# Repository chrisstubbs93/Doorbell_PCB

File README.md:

# Lecturer Availability Door Announcer

## Abstract
Traditionally a student would have to summon a lecturer in a shared office by knocking on the door. This disturbs the other lecturers in the office, and the desired lecturer may not even be present.

A system to alert a specific lecturer to the presence of someone at the door is not currently widely adopted. To investigate how such a system should work, it is crucial to gain insight into the current solutions to the individual technical challenges.

## Introduction
The main aim of this project is to develop a battery-operated device with inputs to receive interaction from the student, and outputs to feed back to the student and lecturer. It is to be fixed to the inside of the door of a multiple occupied lecturer's room. Through this device anyone outside the door shall be able to raise the attention of a single lecturer, and not to everyone in the room (which is what knocking at the door does). When a student operates the device, a notification should be sent to the appropriate lecturer’s mobile phone. It should also be possible for students to see the status/availability of a lecturer from the device, which the lecturer can set.

## Hardware

 - ESP32-WROOM-32
 - Waveshare 2.9" B/W ePaper
 - TCA9548A i2c multiplexer
 - VCNL4020 IR proximity sensor(s)

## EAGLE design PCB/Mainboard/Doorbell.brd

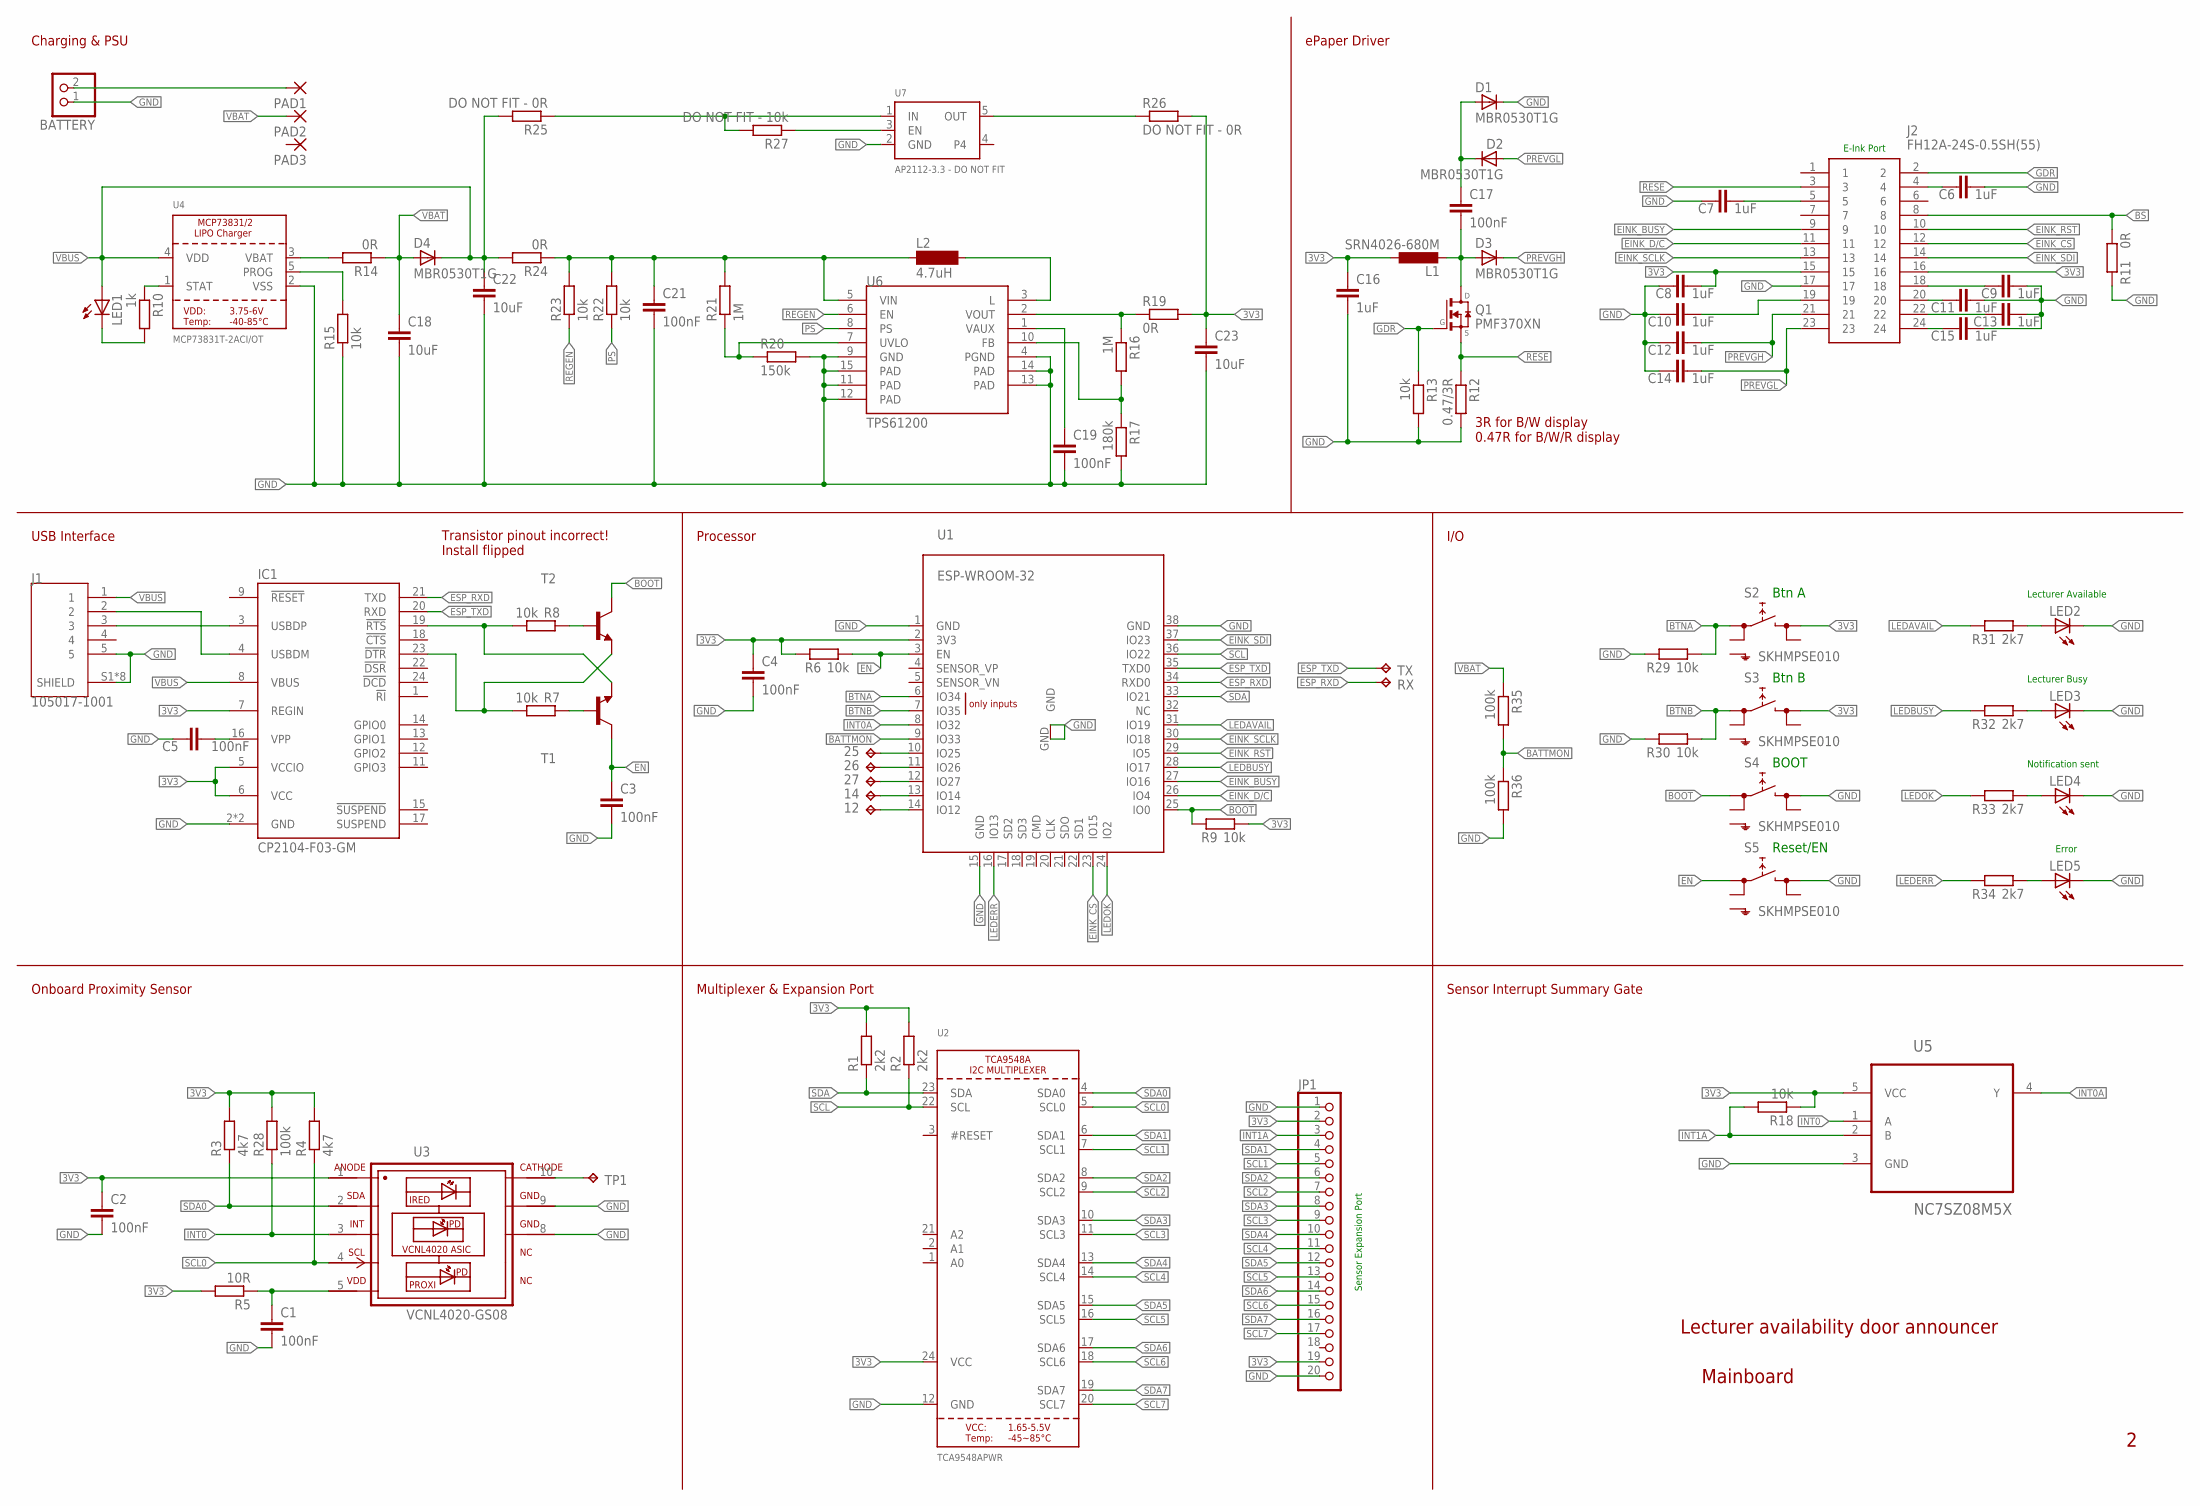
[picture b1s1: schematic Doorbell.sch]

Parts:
12, 14, 25, 26, 27: TPB1,27; B1,27
BATTERY: PINHD-1X2/90; 1X02/90
C1, C2, C3, C4, C5, C17, C19, C21: 100nF; C0603
C6, C7, C8, C9, C10, C11, C12, C13, C14, C15, C16: 1uF; C0603
C18, C22, C23: 10uF; C1206
D1, D2, D3, D4: MBR0530T1G; SOD123
IC1: CP2104-F03-GM; QFN24-PAD
J1: 105017-1001; MOLEX_105017-1001
J2: FH12A-24S-0.5SH(55); FH12A-24S-0.5SH
JP1: PINHD-1X20/90; 1X20/90
L1: SRN4026-680M; L4532P
L2: 4.7uH; MS50
LED1, LED2, LED3, LED4, LED5: LEDSML0603; SML0603
PAD1, PAD2, PAD3: WIREPADSMD1,27-254; SMD1,27-2,54
Q1: PMF370XN; SOT323-R
R1, R2: 2k2; R0603
R3, R4: 4k7; R0603
R5: 10R; R0603
R6, R7, R8, R9, R13, R15, R18, R22, R23, R29, R30: 10k; R0603
R10: 1k; R0603
R11, R14, R19, R24: 0R; R0603
R12: 0.47/3R; R0603
R16, R21: 1M; R0603
R17: 180k; R0603
R20: 150k; R0603
R25, R26: DO NOT FIT - 0R; R0603
R27: DO NOT FIT - 10k; R0603
R28, R35, R36: 100k; R0603
R31, R32, R33, R34: 2k7; R0603
RX: TPB1,27; B1,27
S2, S3, S4, S5: SKHMPSE010; SKHMPXE010
T1, T2: -NPN-SOT23-EBC; SOT23-EBC
TP1: TPB1,27; B1,27
TX: TPB1,27; B1,27
U1: ESP-WROOM-32
U2: TCA9548APWR; TSSOP24
U3: VCNL4020-GS08; PHODET_VCNL4020
U4: MCP73831T-2ACI/OT; SOT23-5
U5: NC7SZ08M5X; SOT95P280X145-5N; DIGI-KEY_PART_NUMBER NC7SZ08M5XCT-ND
U6: TPS61200; QFN-10_PAD
U7: AP2112-3.3 - DO NOT FIT; SOT23-5

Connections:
3V3: C2.1, C4.1, C8.2, C16.1, C23.1, IC1.5 (VCCIO), IC1.6 (VCC), IC1.7 (REGIN), J2.15, J2.16, JP1.2, JP1.19, L1.1, R1.2, R2.2, R3.2, R4.2, R5.2, R6.2, R9.1, R18.1, R19.2, R26.2, R28.2, S2.3 (2.1), S3.3 (2.1), U1.2 (3V3), U2.24 (VCC), U3.1 (IR-ANODE), U5.5 (VCC)
BATTMON: R35.2, R36.1, U1.9 (IO33)
BOOT: R9.2, S4.1 (1.1), T2.C, U1.25 (IO0)
BS: J2.8, R11.1
BTNA: R29.1, S2.1 (1.1), U1.6 (IO34)
BTNB: R30.1, S3.1 (1.1), U1.7 (IO35)
DTR: IC1.23 (!DTR), R7.1, T2.E
EINK_BUSY: J2.9, U1.27 (IO16)
EINK_CS: J2.12, U1.23 (IO15)
EINK_D/C: J2.11, U1.26 (IO4)
EINK_RST: J2.10, U1.29 (IO5)
EINK_SCLK: J2.13, U1.30 (IO18)
EINK_SDI: J2.14, U1.37 (IO23)
EN: C3.1, R6.1, S5.1 (1.1), T1.C, U1.3 (EN)
ESP_RXD: IC1.21 (TXD), RX.TP, U1.34 (RXD0)
ESP_TXD: IC1.20 (RXD), TX.TP, U1.35 (TXD0)
GDR: J2.2, Q1.1 (G), R13.1
GND: BATTERY.1, C1.2, C2.2, C3.2, C4.2, C5.1, C6.2, C7.1, C8.1, C9.2, C10.1, C11.2, C12.1, C13.2, C14.1, C15.2, C16.2, C18.2, C19.2, C21.2, C22.2, C23.2, D1.1 (C), IC1.2 (GND), IC1.TP (GND), J1.5, J1.S1 (SHIELD), J1.S1.1 (SHIELD), J1.S2 (SHIELD), J1.S2.1 (SHIELD), J1.S3 (SHIELD), J1.S4 (SHIELD), J1.S5 (SHIELD), J1.S6 (SHIELD), J2.17, JP1.1, JP1.20, LED2.C, LED3.C, LED4.C, LED5.C, R11.2, R12.2, R13.2, R15.1, R17.2, R20.2, R29.2, R30.2, R36.2, S4.3 (2.1), S5.3 (2.1), U1.1 (GND), U1.15 (GND), U1.38 (GND), U1.GND, U2.12 (GND), U3.8 (GND2), U3.9 (GND), U4.2 (VSS), U5.3 (GND), U6.4 (PGND), U6.9 (GND), U6.11 (PAD), U6.12 (PAD), U6.13 (PAD), U6.14 (PAD), U6.15 (PAD), U7.2 (GND)
INT0: R28.1, U3.3 (INT), U5.1 (A)
INT0A: U1.8 (IO32), U5.4 (Y)
INT1A: JP1.3, R18.2, U5.2 (B)
LEDAVAIL: R31.2, U1.31 (IO19)
LEDBUSY: R32.2, U1.28 (IO17)
LEDERR: R34.2, U1.16 (IO13)
LEDOK: R33.2, U1.24 (IO2)
unnamed: TP1.TP, U3.10 (IR-CATHODE)
unnamed: C1.1, R5.1, U3.5 (VDD)
unnamed: R7.2, T1.B
unnamed: R16.1, R19.1, U6.2 (VOUT)
unnamed: R8.2, T2.B
unnamed: IC1.4 (USBDM), J1.2
unnamed: IC1.3 (USBDP), J1.3
unnamed: C5.2, IC1.16 (VPP)
unnamed: C17.1, D1.2 (A), D2.1 (C)
unnamed: R10.1, U4.1 (STAT)
unnamed: C10.2, J2.19
unnamed: C17.2, D3.2 (A), L1.2, Q1.3 (D)
unnamed: LED1.C, R10.2
unnamed: C15.1, J2.24
unnamed: C13.1, J2.22
unnamed: C11.1, J2.20
unnamed: C9.1, J2.18
unnamed: C6.1, J2.4
unnamed: C7.2, J2.5
unnamed: R14.2, U4.3 (VBAT)
unnamed: R15.2, U4.5 (PROG)
unnamed: BATTERY.2, PAD1.1
unnamed: R16.2, R17.1, U6.10 (FB)
unnamed: C19.1, U6.1 (VAUX)
unnamed: 12.TP, U1.14 (IO12)
unnamed: R20.1, R21.1, U6.7 (UVLO)
unnamed: L2.2, U6.3 (L)
unnamed: R25.1, R27.2, U7.1 (IN)
unnamed: 14.TP, U1.13 (IO14)
unnamed: R27.1, U7.3 (EN)
unnamed: 25.TP, U1.10 (IO25)
unnamed: 26.TP, U1.11 (IO26)
unnamed: 27.TP, U1.12 (IO27)
unnamed: LED5.A, R34.1
unnamed: LED4.A, R33.1
unnamed: LED3.A, R32.1
unnamed: LED2.A, R31.1
OUT: R26.1, U7.5 (OUT)
PREVGH: C12.2, D3.1 (C), J2.21
PREVGL: C14.2, D2.2 (A), J2.23
PS: R22.1, U6.8 (PS)
REGEN: R23.1, U6.6 (EN)
RESE: J2.3, Q1.2 (S), R12.1
RTS: IC1.19 (!RTS), R8.1, T1.E
SCL: R2.1, U1.36 (IO22), U2.22 (SCL)
SCL0: R4.1, U2.5 (SCL0), U3.4 (SCL)
SCL1: JP1.5, U2.7 (SCL1)
SCL2: JP1.7, U2.9 (SCL2)
SCL3: JP1.9, U2.11 (SCL3)
SCL4: JP1.11, U2.14 (SCL4)
SCL5: JP1.13, U2.16 (SCL5)
SCL6: JP1.15, U2.18 (SCL6)
SCL7: JP1.17, U2.20 (SCL7)
SDA: R1.1, U1.33 (IO21), U2.23 (SDA)
SDA0: R3.1, U2.4 (SDA0), U3.2 (SDA)
SDA1: JP1.4, U2.6 (SDA1)
SDA2: JP1.6, U2.8 (SDA2)
SDA3: JP1.8, U2.10 (SDA3)
SDA4: JP1.10, U2.13 (SDA4)
SDA5: JP1.12, U2.15 (SDA5)
SDA6: JP1.14, U2.17 (SDA6)
SDA7: JP1.16, U2.19 (SDA7)
VBAT: C18.1, D4.2 (A), PAD2.1, R14.1, R35.1
VBUS: C22.1, D4.1 (C), IC1.8 (VBUS), J1.1, LED1.A, R24.2, R25.2, U4.4 (VDD)
VIN: C21.1, L2.1, R21.2, R22.2, R23.2, R24.1, U6.5 (VIN)

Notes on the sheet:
Sensor Expansion Port
E-Ink Port
Btn A
Btn B
BOOT
Reset/EN
Lecturer Available
Lecturer Busy
Notification sent
Error
Onboard Proximity Sensor
Multiplexer & Expansion Port
Sensor Interrupt Summary Gate
I/O
Processor
USB Interface
Charging & PSU
ePaper Driver
Mainboard
Lecturer availability door announcer
3R for B/W display 0.47R for B/W/R display
Transistor pinout incorrect! Install flipped

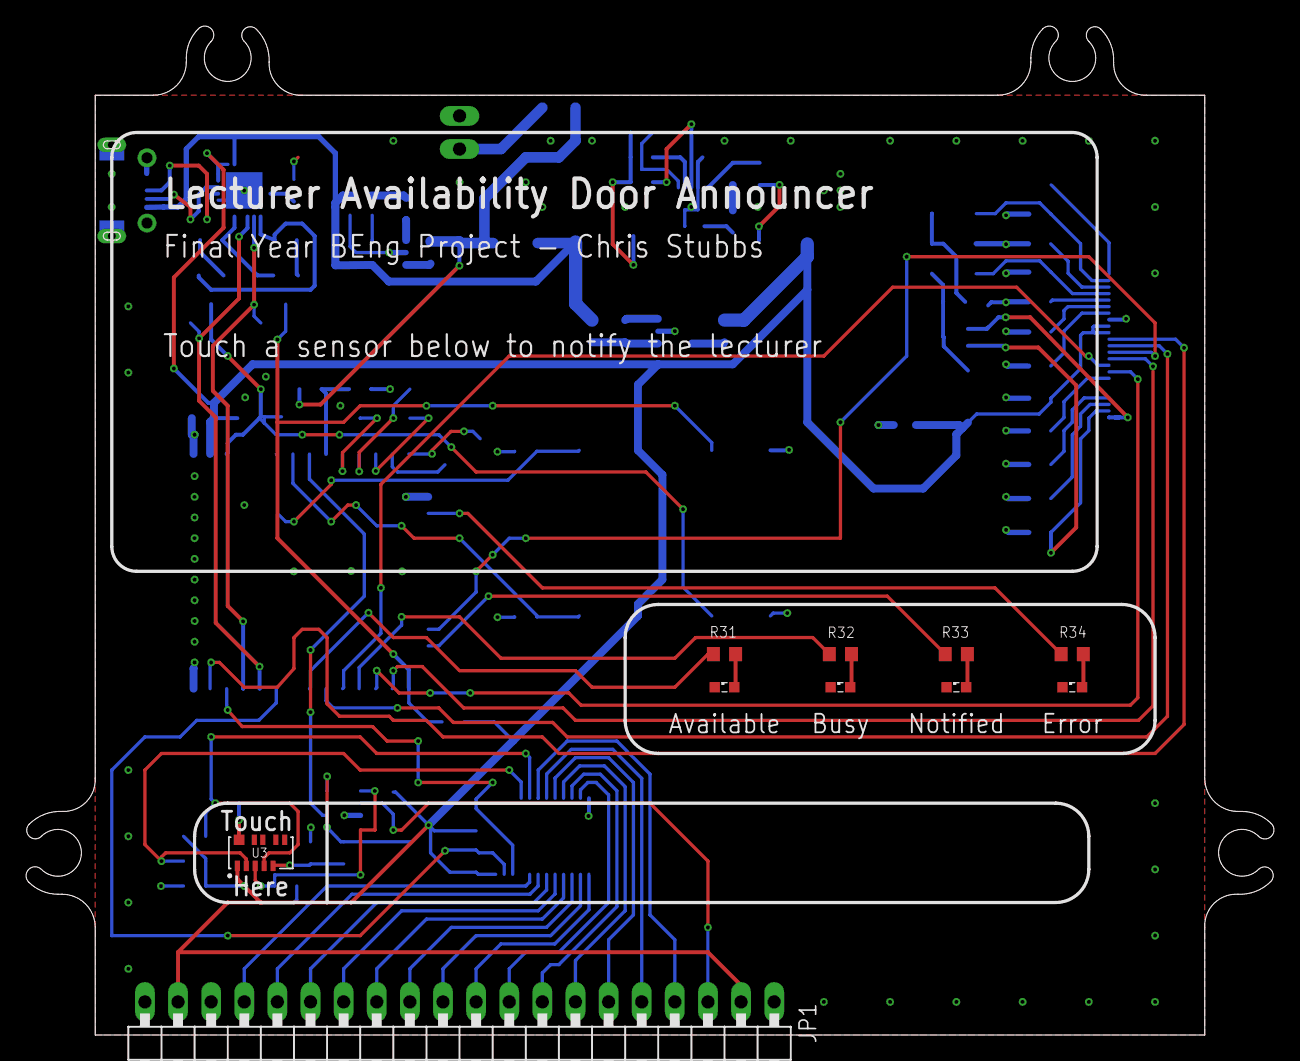
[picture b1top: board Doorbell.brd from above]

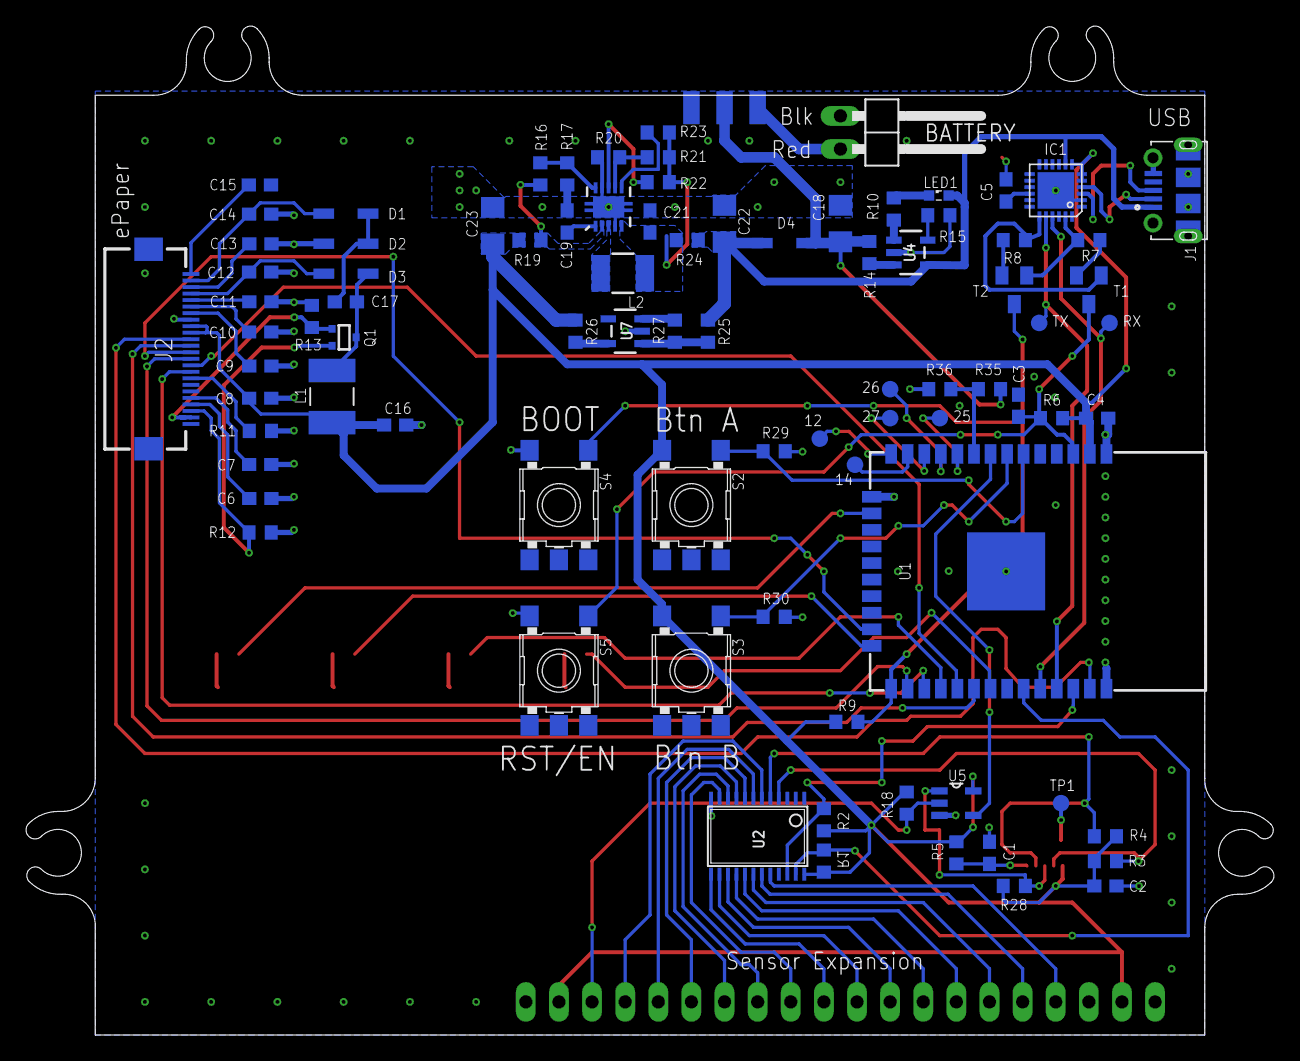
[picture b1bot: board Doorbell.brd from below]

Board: 2 copper layers, 95.7 x 77.4 mm, 99 parts (89 on the bottom side), 90 nets.

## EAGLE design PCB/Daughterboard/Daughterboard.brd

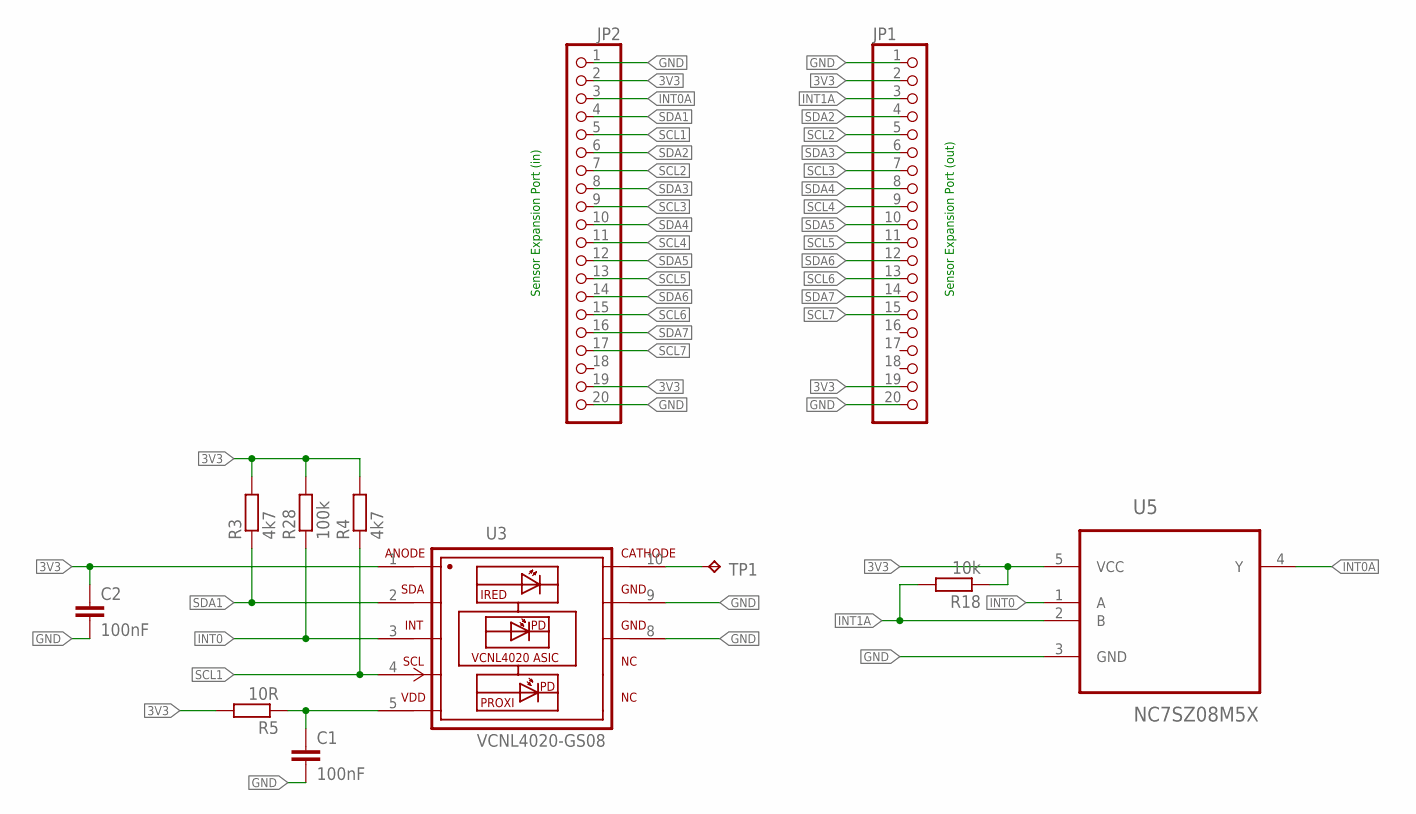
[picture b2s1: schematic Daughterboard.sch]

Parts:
C1, C2: 100nF; C0603
JP1, JP2: PINHD-1X20/90; 1X20/90
R3, R4: 4k7; R0603
R5: 10R; R0603
R18: 10k; R0603
R28: 100k; R0603
TP1: TPB1,27; B1,27
U3: VCNL4020-GS08; PHODET_VCNL4020
U5: NC7SZ08M5X; SOT95P280X145-5N; DIGI-KEY_PART_NUMBER NC7SZ08M5XCT-ND

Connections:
3V3: C2.1, JP1.2, JP1.19, JP2.2, JP2.19, R3.2, R4.2, R5.2, R18.1, R28.2, U3.1 (IR-ANODE), U5.5 (VCC)
GND: C1.2, C2.2, JP1.1, JP1.20, JP2.1, JP2.20, U3.8 (GND2), U3.9 (GND), U5.3 (GND)
INT0: R28.1, U3.3 (INT), U5.1 (A)
INT0A: JP2.3, U5.4 (Y)
INT1A: JP1.3, R18.2, U5.2 (B)
unnamed: TP1.TP, U3.10 (IR-CATHODE)
unnamed: C1.1, R5.1, U3.5 (VDD)
SCL1: JP2.5, R4.1, U3.4 (SCL)
SCL2: JP1.5, JP2.7
SCL3: JP1.7, JP2.9
SCL4: JP1.9, JP2.11
SCL5: JP1.11, JP2.13
SCL6: JP1.13, JP2.15
SCL7: JP1.15, JP2.17
SDA1: JP2.4, R3.1, U3.2 (SDA)
SDA2: JP1.4, JP2.6
SDA3: JP1.6, JP2.8
SDA4: JP1.8, JP2.10
SDA5: JP1.10, JP2.12
SDA6: JP1.12, JP2.14
SDA7: JP1.14, JP2.16

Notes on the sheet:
Sensor Expansion Port (out)
Sensor Expansion Port (in)

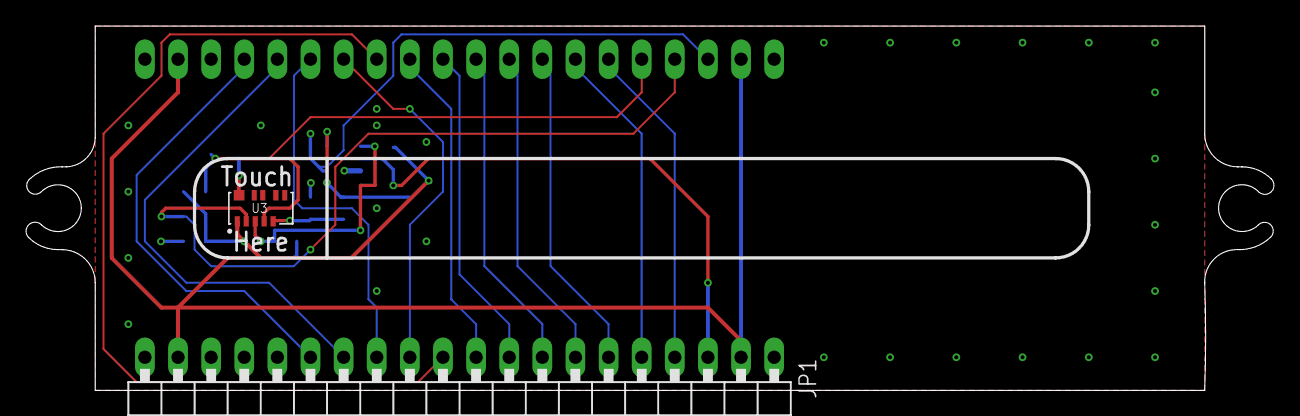
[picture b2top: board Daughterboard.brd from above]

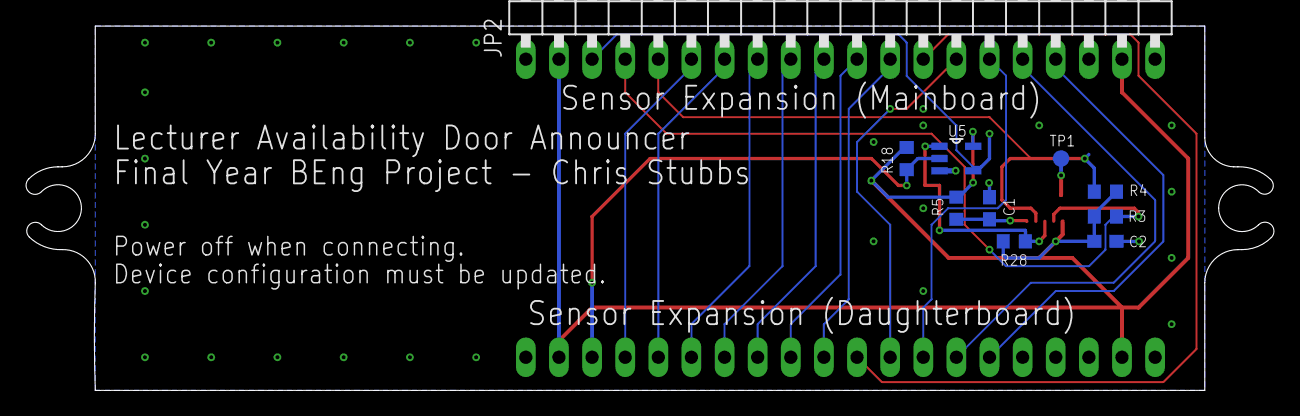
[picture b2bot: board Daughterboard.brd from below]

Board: 2 copper layers, 95.7 x 27.9 mm, 12 parts (10 on the bottom side), 21 nets.

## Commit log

2019-02-10 Commit of V1 PCB files
2019-02-10 First commit of code
    Settings currently stored locally.
2019-02-10 Readme added
2019-02-14 Test of Sphynx documentation
2019-02-14 Schematic titled and tidied
2019-02-20 Add LSBU logo splash
2019-03-03 v0.2: Major tidy, added config file and web portals
    Code tidied into functions, grouped and put in seperate files for easier readability.
    Redundant code removed.
    Config file stored on SPI flash filesystem.
    Wifi setup wizard added.
    Config web portal added.
    Todo: WPA2-Enterprise
2019-03-15 Fixed eduroam
    Fixed some GPIO mapping.
    Added status to web config page.
    Fixed eduroam support.
2019-03-18 WiFi connection attempts, GUI, Batt %.
    Makes 3 wifi connection attempts before falling back to config mode.
    Improvements to GUI.
    Fixed battery percentage.
2019-03-27 v0.6
    Added rot function.
    Can choose to notify if busy.
    Long text is wrapped.
2019-04-03 v1.0
    Major release. Everything is complete and working.
    Power saving implemented.
2019-04-04 v1.1
    Comments reformatted for doxygen. Docs generated.
2019-04-09 Docs generated by doxygen
2019-04-15 PCB rev2 uploaded

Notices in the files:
parts and their libraries:
microbuilder: This work is placed in the public domain, and may be freely used for commercial and non-commercial work with the following conditions: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
